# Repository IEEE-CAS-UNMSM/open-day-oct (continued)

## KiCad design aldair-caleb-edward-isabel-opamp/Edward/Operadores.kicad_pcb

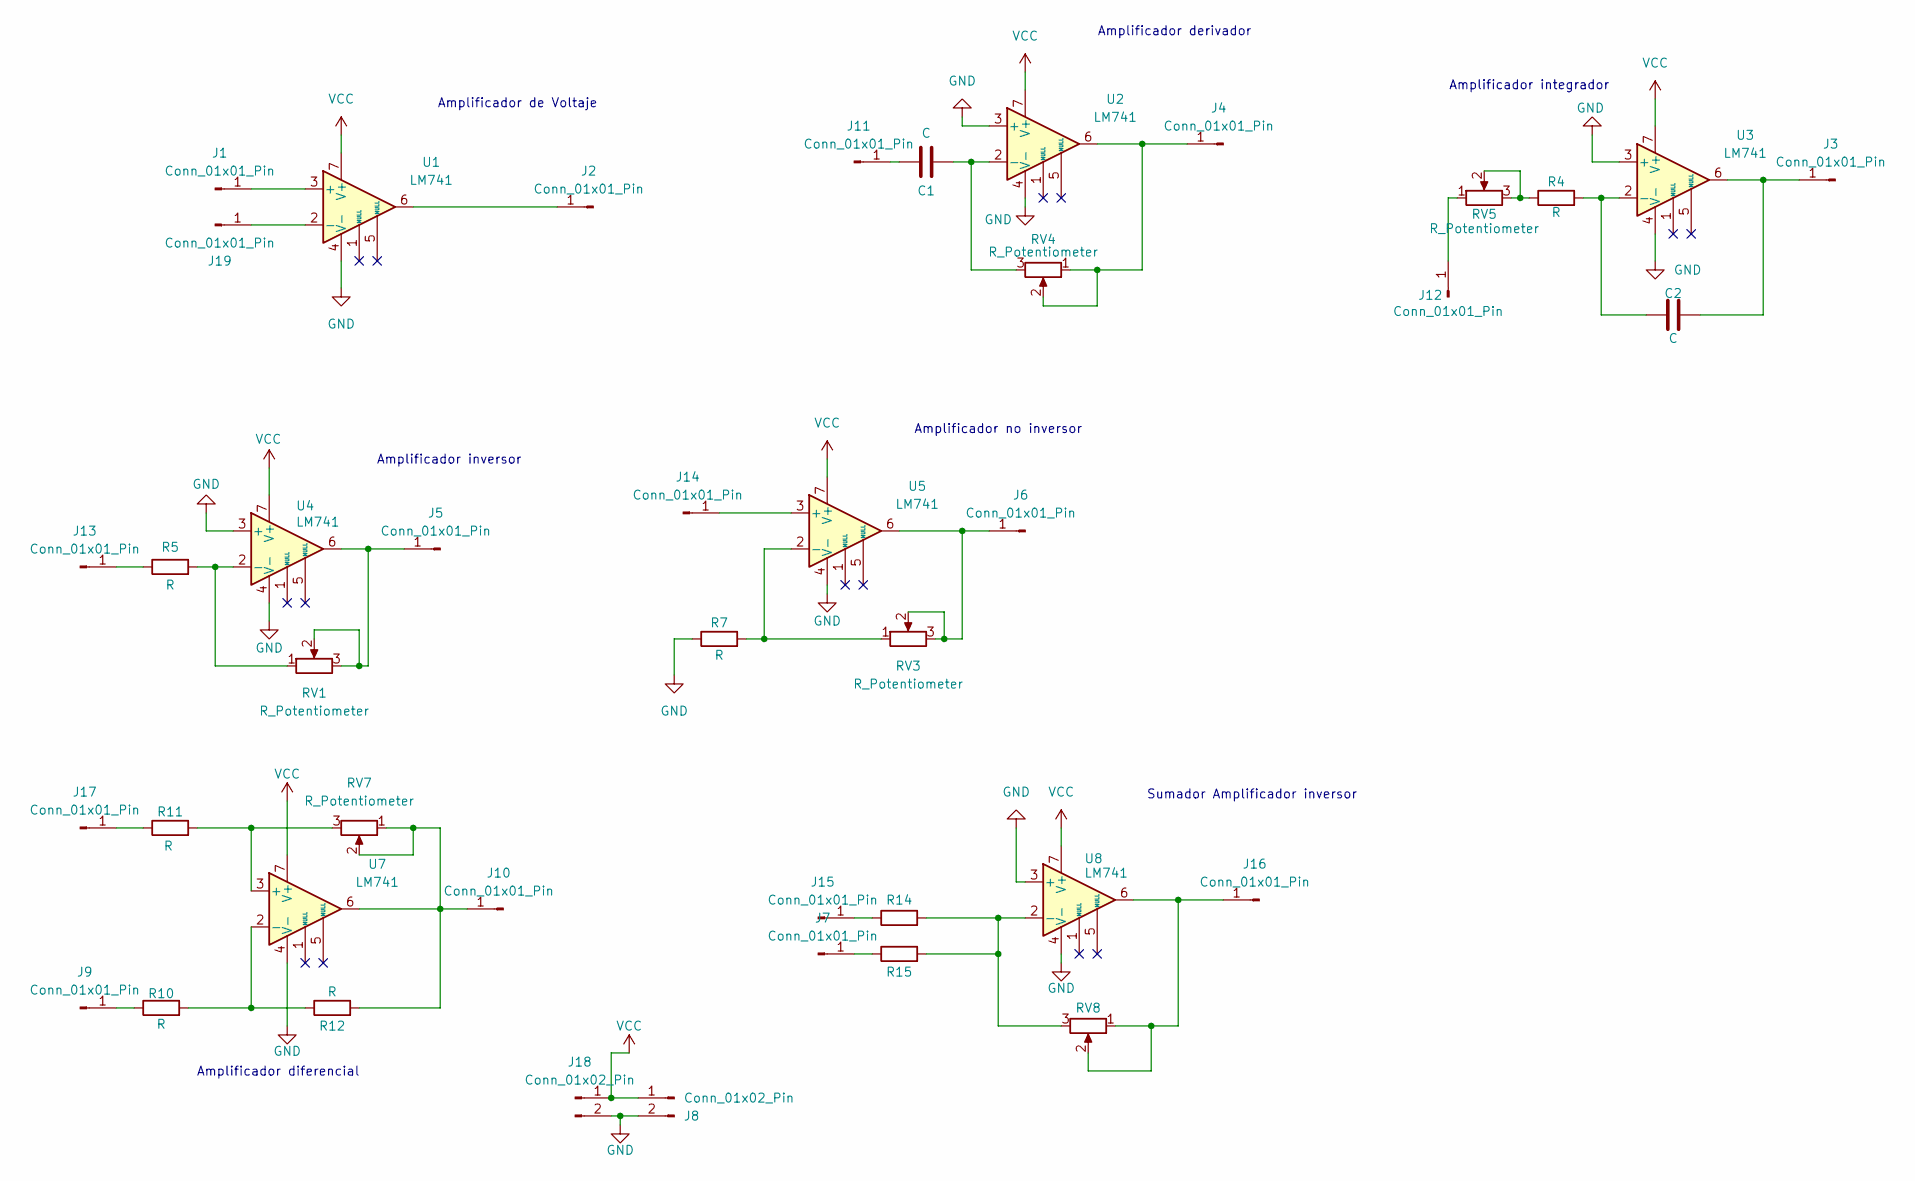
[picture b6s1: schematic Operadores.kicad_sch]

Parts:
C1, C2: C; C_Disc_D5.1mm_W3.2mm_P5.00mm
J1, J2, J3, J4, J5, J6, J7, J9, J10, J11, J12, J13, J14, J15, J16, J17, J19: Conn_01x01_Pin; PinSocket_1x01_P2.54mm_Vertical
J8, J18: Conn_01x02_Pin; PinHeader_1x02_P2.54mm_Vertical
R4, R5, R7, R10, R11, R12, R14, R15: R; R_Axial_DIN0207_L6.3mm_D2.5mm_P10.16mm_Horizontal
RV1, RV3, RV4, RV5, RV7, RV8: R_Potentiometer; Potentiometer_Omeg_PC16BU_Vertical
U1, U2, U3, U4, U5, U7, U8: LM741; DIP-8_W7.62mm_Socket_LongPads

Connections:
GND: J8.2, J18.2, R7.1, U1.4 (V-), U2.3 (+), U2.4 (V-), U3.3 (+), U3.4 (V-), U4.3 (+), U4.4 (V-), U5.4 (V-), U7.4 (V-), U8.3 (+), U8.4 (V-); also elsewhere on the board
unnamed: J1.1, U1.3 (+)
unnamed: J2.1, U1.6
unnamed: C2.2, J3.1, U3.6
unnamed: J4.1, RV4.1, RV4.2, U2.6
unnamed: J5.1, RV1.2, RV1.3, U4.6
unnamed: J6.1, RV3.2, RV3.3, U5.6
unnamed: J7.1, R15.1
unnamed: J9.1, R10.1
unnamed: J10.1, R12.2, RV7.1, RV7.2, U7.6
unnamed: C1.1, J11.1
unnamed: J12.1, RV5.1
unnamed: J13.1, R5.1
unnamed: J14.1, U5.3 (+)
unnamed: J15.1, R14.1
unnamed: J16.1, RV8.1, RV8.2, U8.6
unnamed: J17.1, R11.1
unnamed: J19.1, U1.2 (-)
unnamed: R4.1, RV5.2, RV5.3
unnamed: C1.2, RV4.3, U2.2 (-)
unnamed: C2.1, R4.2, U3.2 (-)
unnamed: R5.2, RV1.1, U4.2 (-)
unnamed: R7.2, RV3.1, U5.2 (-)
unnamed 23: R11.2, RV7.3, U7.3 (+); also elsewhere on the board
unnamed: R10.2, R12.1, U7.2 (-)
unnamed: R14.2, R15.2, RV8.3, U8.2 (-)
VCC: J8.1, J18.1, U1.7 (V+), U2.7 (V+), U3.7 (V+), U4.7 (V+), U5.7 (V+), U7.7 (V+), U8.7 (V+)

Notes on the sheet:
Amplificador derivador
Amplificador diferencial
Amplificador integrador
Amplificador de Voltaje
Amplificador inversor
Amplificador no inversor
Sumador Amplificador inversor

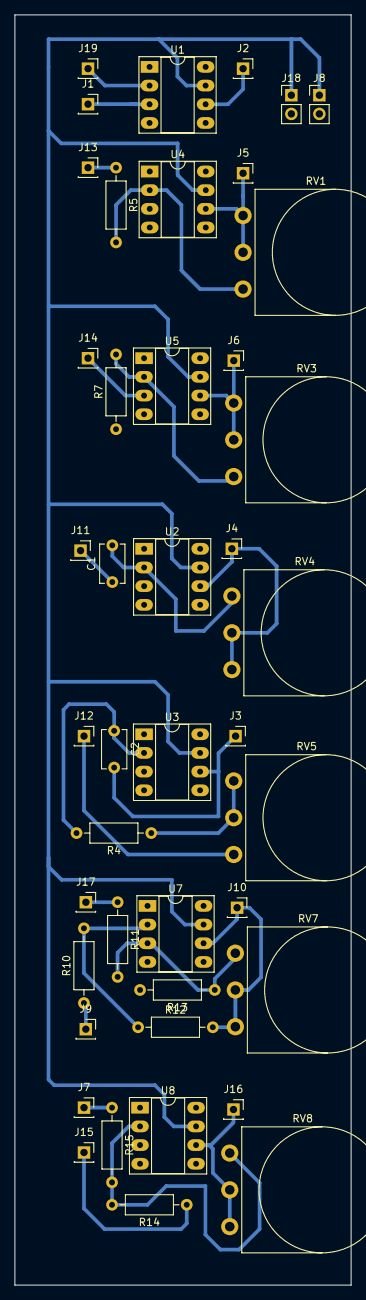
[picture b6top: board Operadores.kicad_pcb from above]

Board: 2 copper layers, 45.7 x 172.7 mm, 43 parts (0 on the bottom side), 27 nets.

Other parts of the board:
R13: R; R_Axial_DIN0207_L6.3mm_D2.5mm_P10.16mm_Horizontal

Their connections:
GND: R13.2; also elsewhere on the board
unnamed 23: R13.1; also elsewhere on the board

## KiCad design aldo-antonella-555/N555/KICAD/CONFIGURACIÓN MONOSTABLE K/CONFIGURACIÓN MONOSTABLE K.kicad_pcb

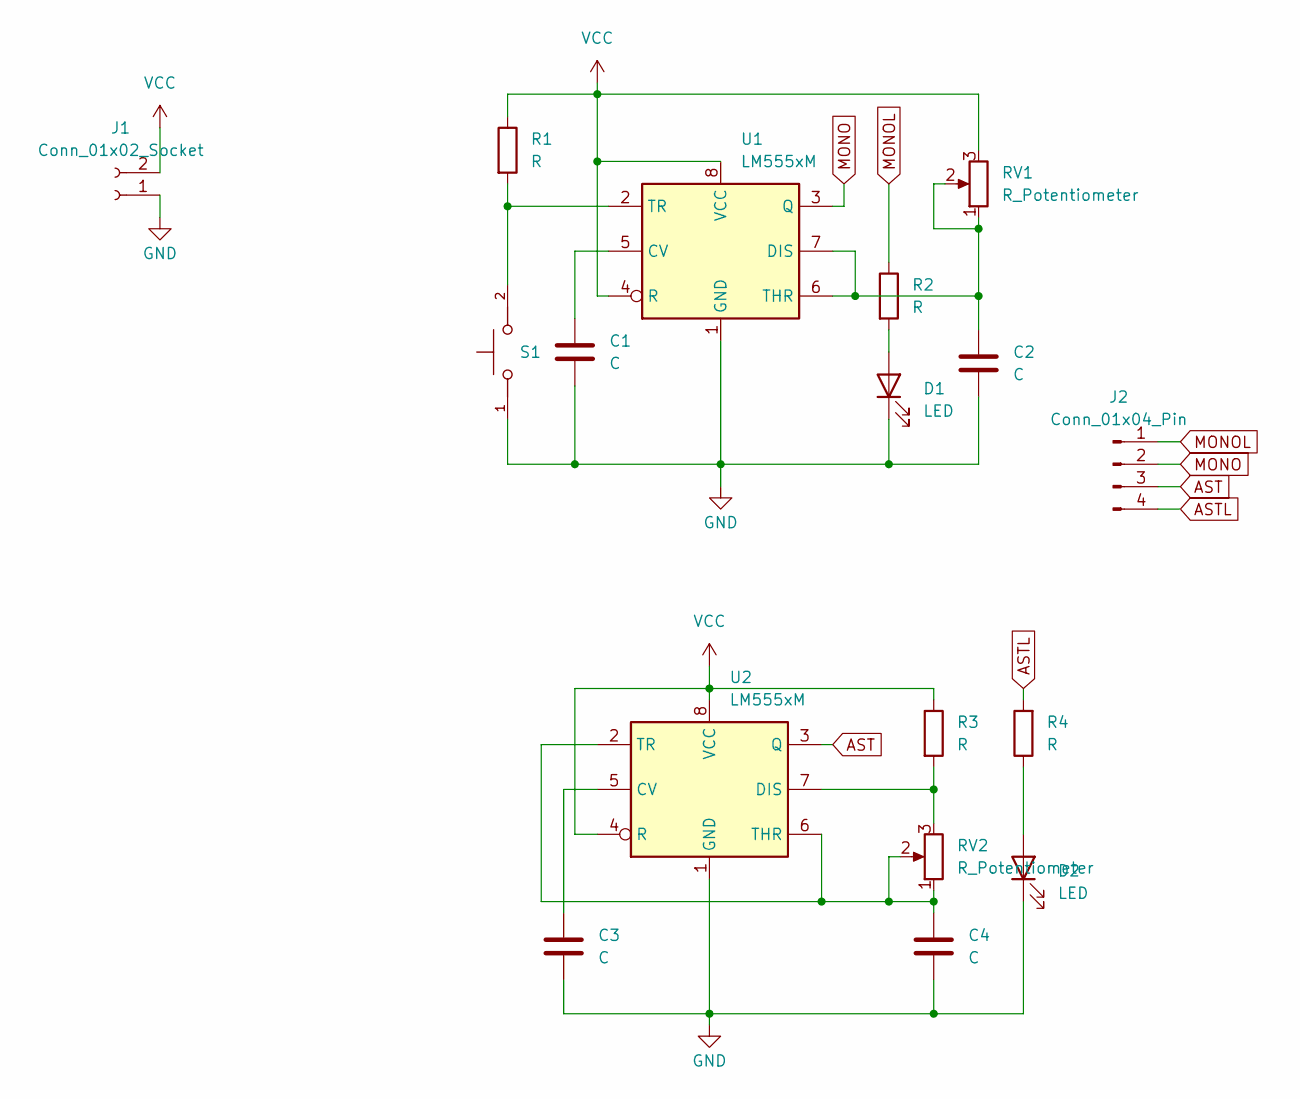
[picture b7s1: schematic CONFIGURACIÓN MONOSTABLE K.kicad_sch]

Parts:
C1, C2, C3, C4: C; CP_Radial_Tantal_D4.5mm_P5.00mm
D1, D2: LED; LED_D8.0mm
J1: Conn_01x02_Socket; PinHeader_1x02_P2.54mm_Vertical
J2: Conn_01x04_Pin; PinHeader_1x04_P2.54mm_Vertical
R1, R2, R3, R4: R; R_Axial_DIN0207_L6.3mm_D2.5mm_P10.16mm_Horizontal
RV1, RV2: R_Potentiometer; Potentiometer_Omeg_PC16BU_Vertical
S1: TL59NF160Q; SW_TL59NF160Q; PARTREV G
U1, U2: LM555xM; DIP-8_W7.62mm_LongPads

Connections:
AST: J2.3, U2.3 (Q)
ASTL: J2.4, R4.2
GND: C1.2, C2.2, C3.2, C4.2, D1.1 (K), D2.1 (K), J1.1, S1.1, U1.1 (GND), U2.1 (GND)
MONO: J2.2, U1.3 (Q)
MONOL: J2.1, R2.1
unnamed: D1.2 (A), R2.2
unnamed: D2.2 (A), R4.1
unnamed: C1.1, U1.5 (CV)
unnamed: C2.1, RV1.1, RV1.2, U1.6 (THR), U1.7 (DIS)
unnamed: R1.2, S1.2, U1.2 (TR)
unnamed: C3.1, U2.5 (CV)
unnamed: R3.2, RV2.3, U2.7 (DIS)
unnamed: C4.1, RV2.1, RV2.2, U2.2 (TR), U2.6 (THR)
VCC: J1.2, R1.1, R3.1, RV1.3, U1.4 (R), U1.8 (VCC), U2.4 (R), U2.8 (VCC)

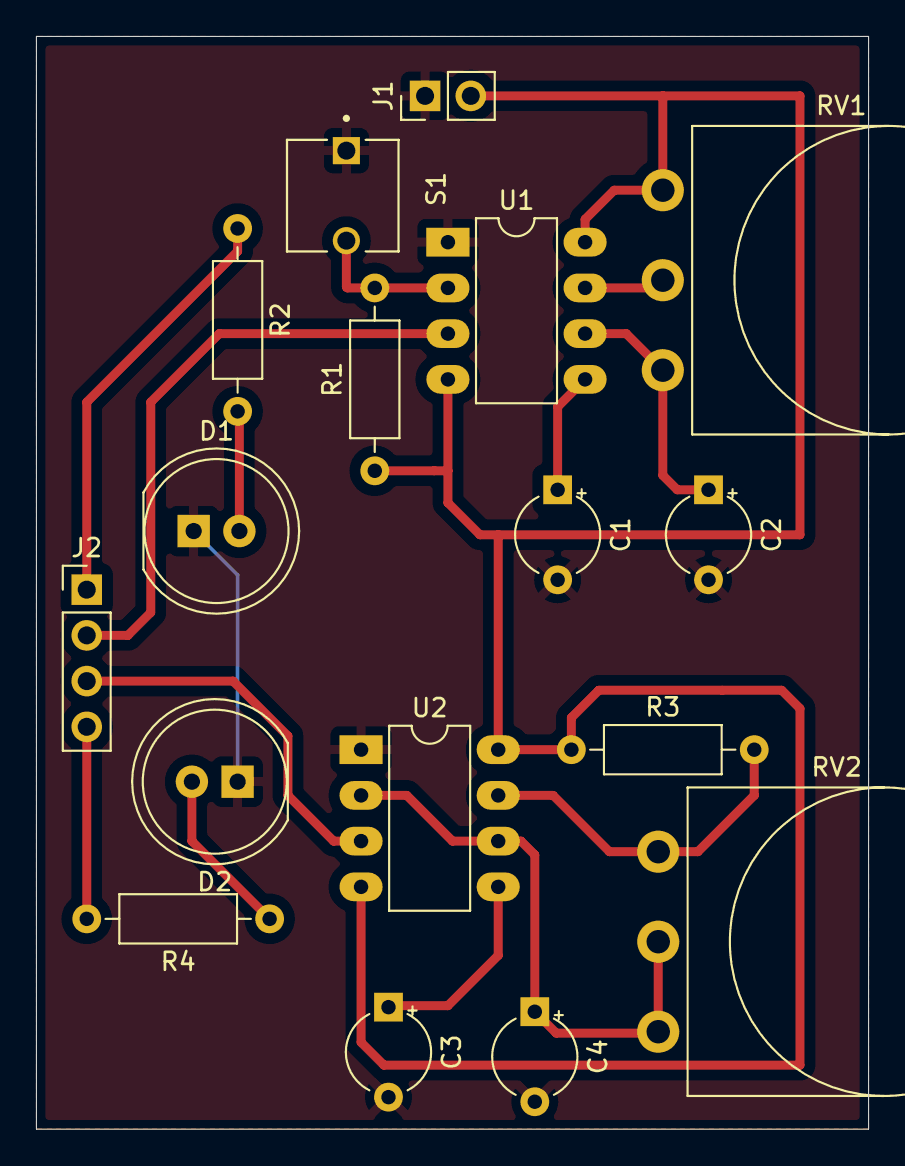
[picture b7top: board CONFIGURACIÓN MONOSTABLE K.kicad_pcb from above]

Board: 2 copper layers, 46.2 x 60.7 mm, 17 parts (0 on the bottom side), 14 nets.

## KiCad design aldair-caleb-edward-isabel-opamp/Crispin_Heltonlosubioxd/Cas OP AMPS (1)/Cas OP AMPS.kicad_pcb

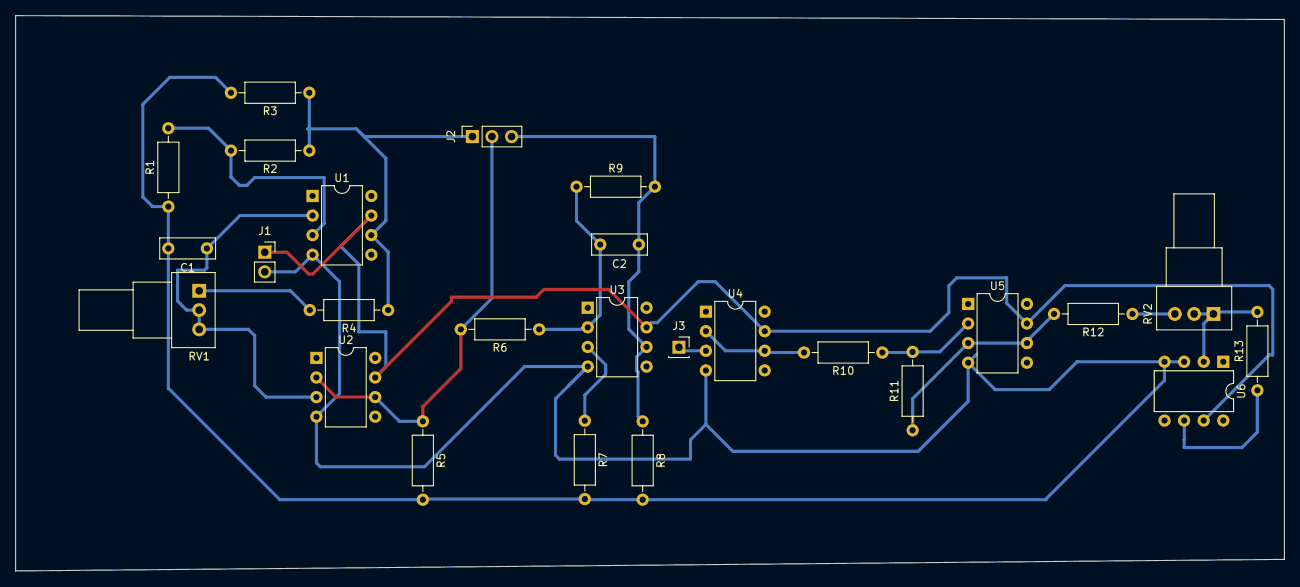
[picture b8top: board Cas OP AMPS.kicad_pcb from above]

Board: 2 copper layers, 164.5 x 72.0 mm, 26 parts (0 on the bottom side), 17 nets.

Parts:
C1: 1uF; C_Disc_D7.0mm_W2.5mm_P5.00mm
C2: 0.2uF; C_Disc_D7.0mm_W2.5mm_P5.00mm
J1: Conn_01x02_Pin; PinSocket_1x02_P2.54mm_Vertical
J2: Conn_01x03_Pin; PinSocket_1x03_P2.54mm_Vertical
J3: Conn_01x01_Pin; PinSocket_1x01_P2.54mm_Vertical
R1: 20K; R_Axial_DIN0207_L6.3mm_D2.5mm_P10.16mm_Horizontal
R2, R9: 100K; R_Axial_DIN0207_L6.3mm_D2.5mm_P10.16mm_Horizontal
R3, R5: 4.7K; R_Axial_DIN0207_L6.3mm_D2.5mm_P10.16mm_Horizontal
R4: 100; R_Axial_DIN0207_L6.3mm_D2.5mm_P10.16mm_Horizontal
R6: 30K; R_Axial_DIN0207_L6.3mm_D2.5mm_P10.16mm_Horizontal
R7: 100k; R_Axial_DIN0207_L6.3mm_D2.5mm_P10.16mm_Horizontal
R8, R10: 4.7k; R_Axial_DIN0207_L6.3mm_D2.5mm_P10.16mm_Horizontal
R11: 10k; R_Axial_DIN0207_L6.3mm_D2.5mm_P10.16mm_Horizontal
R12, R13: 1k; R_Axial_DIN0207_L6.3mm_D2.5mm_P10.16mm_Horizontal
RV1: 100K; Potentiometer_Alps_RK09Y11_Single_Horizontal
RV2: 100k; Potentiometer_Alps_RK09Y11_Single_Horizontal
U1, U2, U3, U4, U5, U6: LM741; DIP-8_W7.62mm

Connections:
+12: J1.1, U1.7 (V+), U2.7 (V+), U3.7 (V+), U4.7 (V+), U5.7 (V+), U6.7 (V+)
Earth: C1.2, J1.2, R1.1, R3.2, R5.2, R7.2, R8.2, U1.4 (V-), U2.4 (V-), U3.4 (V-), U4.4 (V-), U5.4 (V-), U6.3 (+), U6.4 (V-)
unnamed: J2.1, R2.1, R3.1, R4.1, U1.6
unnamed: J2.2, R5.1, R6.2, U2.2 (-), U2.6
unnamed: C2.1, J2.3, R8.1, R9.2, U3.6
unnamed: J3.1, U4.3 (+)
unnamed: R4.2, RV1.1
unnamed: R12.1, RV2.3
unnamed: R13.1, U6.6
unnamed: R1.2, R2.2, U1.3 (+)
unnamed: C1.1, RV1.2, RV1.3, U1.2 (-), U2.3 (+)
unnamed: R7.1, U3.3 (+)
unnamed: C2.2, R6.1, R9.1, U3.2 (-)
unnamed: R10.2, U4.2 (-), U4.6
unnamed: R11.1, R12.2, U5.3 (+), U5.6
unnamed: R10.1, R11.2, U5.2 (-)
unnamed: R13.2, RV2.1, RV2.2, U6.2 (-)

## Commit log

2024-09-29 Desarrollo helton
2024-09-29 Desarrollo Eduardo
2024-09-29 Desarrollo Julio
2024-09-29 Desarrollo Sebastian
2024-09-29 Desarrollo grupo 1
2024-09-29 Desarollo grupo 2
2024-09-29 Desarrollo Gabriela
2024-09-29 Desarrollo grupo 3
2024-09-29 Desarrollo Bryan
2024-09-29 Avance Bryan
2024-09-29 Cambios Bryan
2024-09-29 Cambios
2024-09-29 De nuevo
2024-09-29 cambios bryans ada
2024-09-29 cambios aldo
2024-09-29 cambios antonella
2024-09-29 cambios Ivan
2024-09-30 Trabajo de amplificadores de edward
2024-09-30 Cambios
    Se agrega el esquematico y diseño PCB en kicad del cronometro/temporizador de 0 a 999
2024-09-30 Agregar
    archivos comprimidos
2024-09-30 ojala haya funcionado
2024-09-30 Avance Caleb XR2206
2024-09-30 cambios eduardo
    Actualizacion
2024-10-01 Cambios Julio
2024-10-01 cambiso antes del merge
2024-10-01 Subiendo KidCad-Crispin-OPAM
2024-10-01 Cambios Finales Prueba OP AMP - EDWARDS
2024-10-01 parte del timer 555
2024-10-01 CASI FINAL
2024-10-01 Hola
2024-10-01 Hola cambios final
